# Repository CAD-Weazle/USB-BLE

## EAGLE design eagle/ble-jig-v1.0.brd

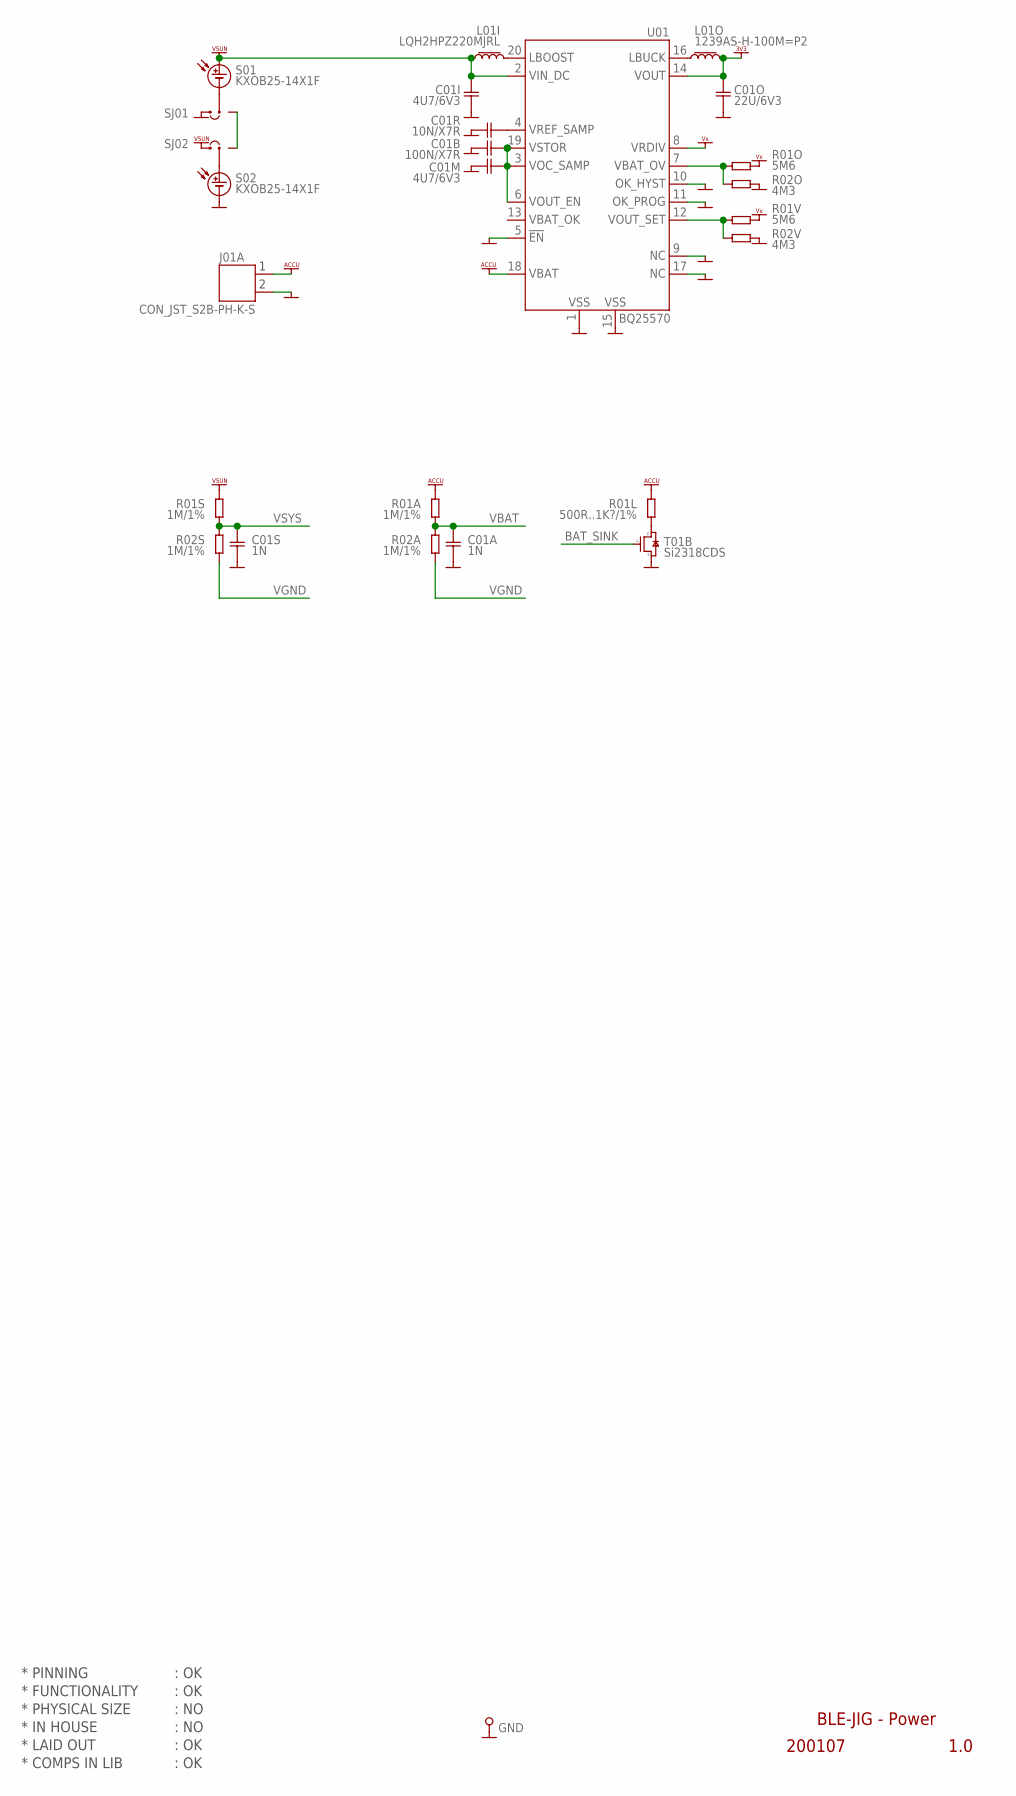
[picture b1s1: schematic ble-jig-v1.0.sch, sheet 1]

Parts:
C01A, C01S: 1N; CAP0402
C01B: 100N/X7R; CAP0402
C01I, C01M: 4U7/6V3; CAP0402
C01O: 22U/6V3; CAP0402
C01R: 10N/X7R; CAP0402
GND: PIN_TEST; HOLE_PTH_0.8MM
J01A: CON_JST_S2B-PH-K-S
L01I: LQH2HPZ220MJRL; L_1008
L01O: 1239AS-H-100M=P2; L_1008
R01A, R01S, R02A, R02S: 1M/1%; RES0402
R01L: 500R..1K?/1%; RES0603
R01O, R01V: 5M6; RES0402
R02O, R02V: 4M3; RES0402
S01, S02: KXOB25-14X1F
SJ01, SJ02: SJ3SJ3-S; SJ3-S
T01B: Si2318CDS; NFET_SOT23
U01: BQ25570; VQFN20

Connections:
ACCU: J01A.1, R01A.2, R01L.2, U01.18 (18.VBAT)
BAT_SINK: T01B.1 (G1); also elsewhere on the board
GND: C01A.2, C01B.2, C01I.2, C01M.2, C01O.2, C01R.2, C01S.2, GND.1, J01A.2, R02O.2, R02V.2, S02.2, SJ01.1, T01B.2 (S2), U01.1 (1.VSS), U01.5 (5.!EN), U01.9 (9.NC), U01.10 (10.OK_HYST), U01.11 (11.OK_PROG), U01.15 (15.VSS), U01.17 (17.NC), U01.TP (15.VSS), U01.V1 (15.VSS), U01.V2 (15.VSS), U01.V3 (15.VSS), U01.V4 (15.VSS); also elsewhere on the board
unnamed: S01.2, SJ01.2
unnamed: S02.1, SJ02.2
unnamed: SJ01.3, SJ02.3
unnamed: R01L.1, T01B.3 (D3)
unnamed: C01R.1, U01.4 (4.VREF_SAMP)
unnamed: L01I.2, U01.20 (20.LBOOST)
unnamed: L01O.1, U01.16 (16.LBUCK)
VBAT: C01A.1, R01A.1, R02A.2; also elsewhere on the board
VBAT_OV: R01O.2, R02O.1, U01.7 (7.VBAT_OV)
VDD_3V3: C01O.1, L01O.2, U01.14 (14.VOUT); also elsewhere on the board
VGND: R02A.1, R02S.1; also elsewhere on the board
VOUT_SET: R01V.2, R02V.1, U01.12 (12.VOUT_SET)
VSTOR: C01B.1, C01M.1, U01.3 (3.VOC_SAMP), U01.6 (6.VOUT_EN), U01.19 (19.VSTOR)
VSUN: C01I.1, L01I.1, R01S.2, S01.1, SJ02.1, U01.2 (2.VIN_DC)
VSYS: C01S.1, R01S.1, R02S.2; also elsewhere on the board
VX: R01O.1, R01V.1, U01.8 (8.VRDIV)

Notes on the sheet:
* PINNING
* FUNCTIONALITY
* PHYSICAL SIZE
* LAID OUT
* COMPS IN LIB
* IN HOUSE
BLE-JIG - Power
200107
1.0
: OK
: NO

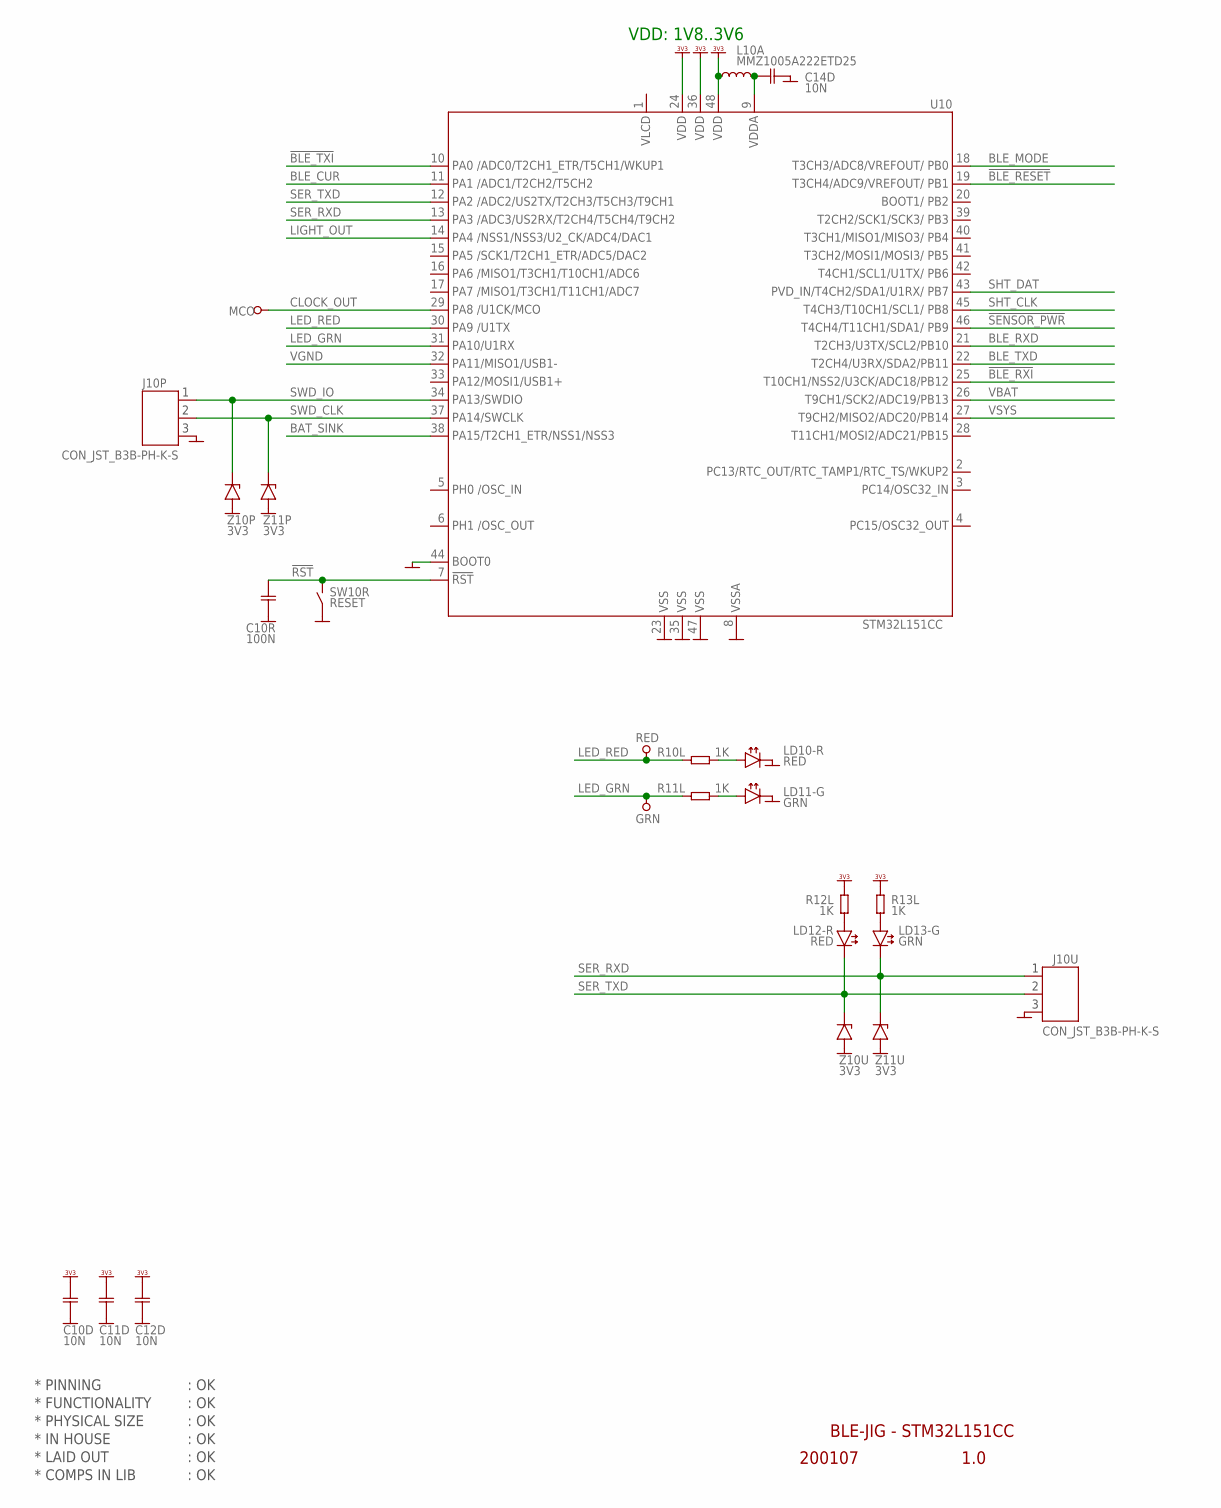
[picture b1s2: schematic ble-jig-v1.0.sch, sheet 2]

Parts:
C10D, C11D, C12D, C14D: 10N; CAP0402
C10R: 100N; CAP0402
GRN: PIN_TEST_0.6MM; HOLE_PTH_0.6MM
J10P, J10U: CON_JST_B3B-PH-K-S
L10A: MMZ1005A222ETD25; L_0402
LD10-R, LD12-R: RED; LED_SMD_0603
LD11-G, LD13-G: GRN; LED_SMD_0603
MCO: PIN_TEST; HOLE_PTH_0.8MM
R10L, R11L, R12L, R13L: 1K; RES0402
RED: PIN_TEST_0.6MM; HOLE_PTH_0.6MM
SW10R: RESET; SWITCH_PUSHBUTTON_EVP-AVAA1A
U10: STM32L151CC; LQFP48
Z10P, Z10U, Z11P, Z11U: 3V3; ZENER_SOD80

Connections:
!BLE_RESET: U10.19 (19.PB1); also elsewhere on the board
!BLE_RXI: U10.25 (25.PB12); also elsewhere on the board
!BLE_TXI: U10.10 (10.PA0); also elsewhere on the board
!RST: C10R.1, SW10R.1 (1-2), U10.7 (7.!RST)
!SENSOR_PWR: U10.46 (46.PB9); also elsewhere on the board
BAT_SINK: U10.38 (38.PA15); also elsewhere on the board
BLE_CUR: U10.11 (11.PA1); also elsewhere on the board
BLE_MODE: U10.18 (18.PB0); also elsewhere on the board
BLE_RXD: U10.21 (21.PB10); also elsewhere on the board
BLE_TXD: U10.22 (22.PB11); also elsewhere on the board
CLOCK_OUT: MCO.1, U10.29 (29.PA8)
GND: C10D.2, C10R.2, C11D.2, C12D.2, C14D.2, J10P.3, J10U.3, LD10-R.C, LD11-G.C, SW10R.2 (3-4), U10.8 (8.GND), U10.23 (23.GND), U10.35 (35.GND), U10.44 (44.BOOT0), U10.47 (47.GND), Z10P.1 (+), Z10U.1 (+), Z11P.1 (+), Z11U.1 (+); also elsewhere on the board
LED_GRN: GRN.1, R11L.1, U10.31 (31.PA10)
LED_RED: R10L.1, RED.1, U10.30 (30.PA9)
LIGHT_OUT: U10.14 (14.PA4); also elsewhere on the board
unnamed: LD13-G.A, R13L.2
unnamed: LD12-R.A, R12L.2
unnamed: LD11-G.A, R11L.2
unnamed: LD10-R.A, R10L.2
SER_RXD: J10U.1, LD13-G.C, U10.13 (13.PA3), Z11U.2 (-)
SER_TXD: J10U.2, LD12-R.C, U10.12 (12.PA2), Z10U.2 (-)
SHT_CLK: U10.45 (45.PB8); also elsewhere on the board
SHT_DAT: U10.43 (43.PB7); also elsewhere on the board
SWD_CLK: J10P.2, U10.37 (37.PA14), Z11P.2 (-)
SWD_IO: J10P.1, U10.34 (34.PA13), Z10P.2 (-)
VBAT: U10.26 (26.PB13); also elsewhere on the board
VDDA: C14D.1, L10A.2, U10.9 (9.VDD)
VDD_3V3: C10D.1, C11D.1, C12D.1, L10A.1, R12L.1, R13L.1, U10.24 (24.VDD), U10.36 (36.VDD), U10.48 (48.VDD); also elsewhere on the board
VGND: U10.32 (32.PA11); also elsewhere on the board
VSYS: U10.27 (27.PB14); also elsewhere on the board

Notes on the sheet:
* PINNING
* FUNCTIONALITY
* PHYSICAL SIZE
* LAID OUT
* COMPS IN LIB
* IN HOUSE
: OK
BLE-JIG - STM32L151CC
200107
1.0
VDD: 1V8..3V6

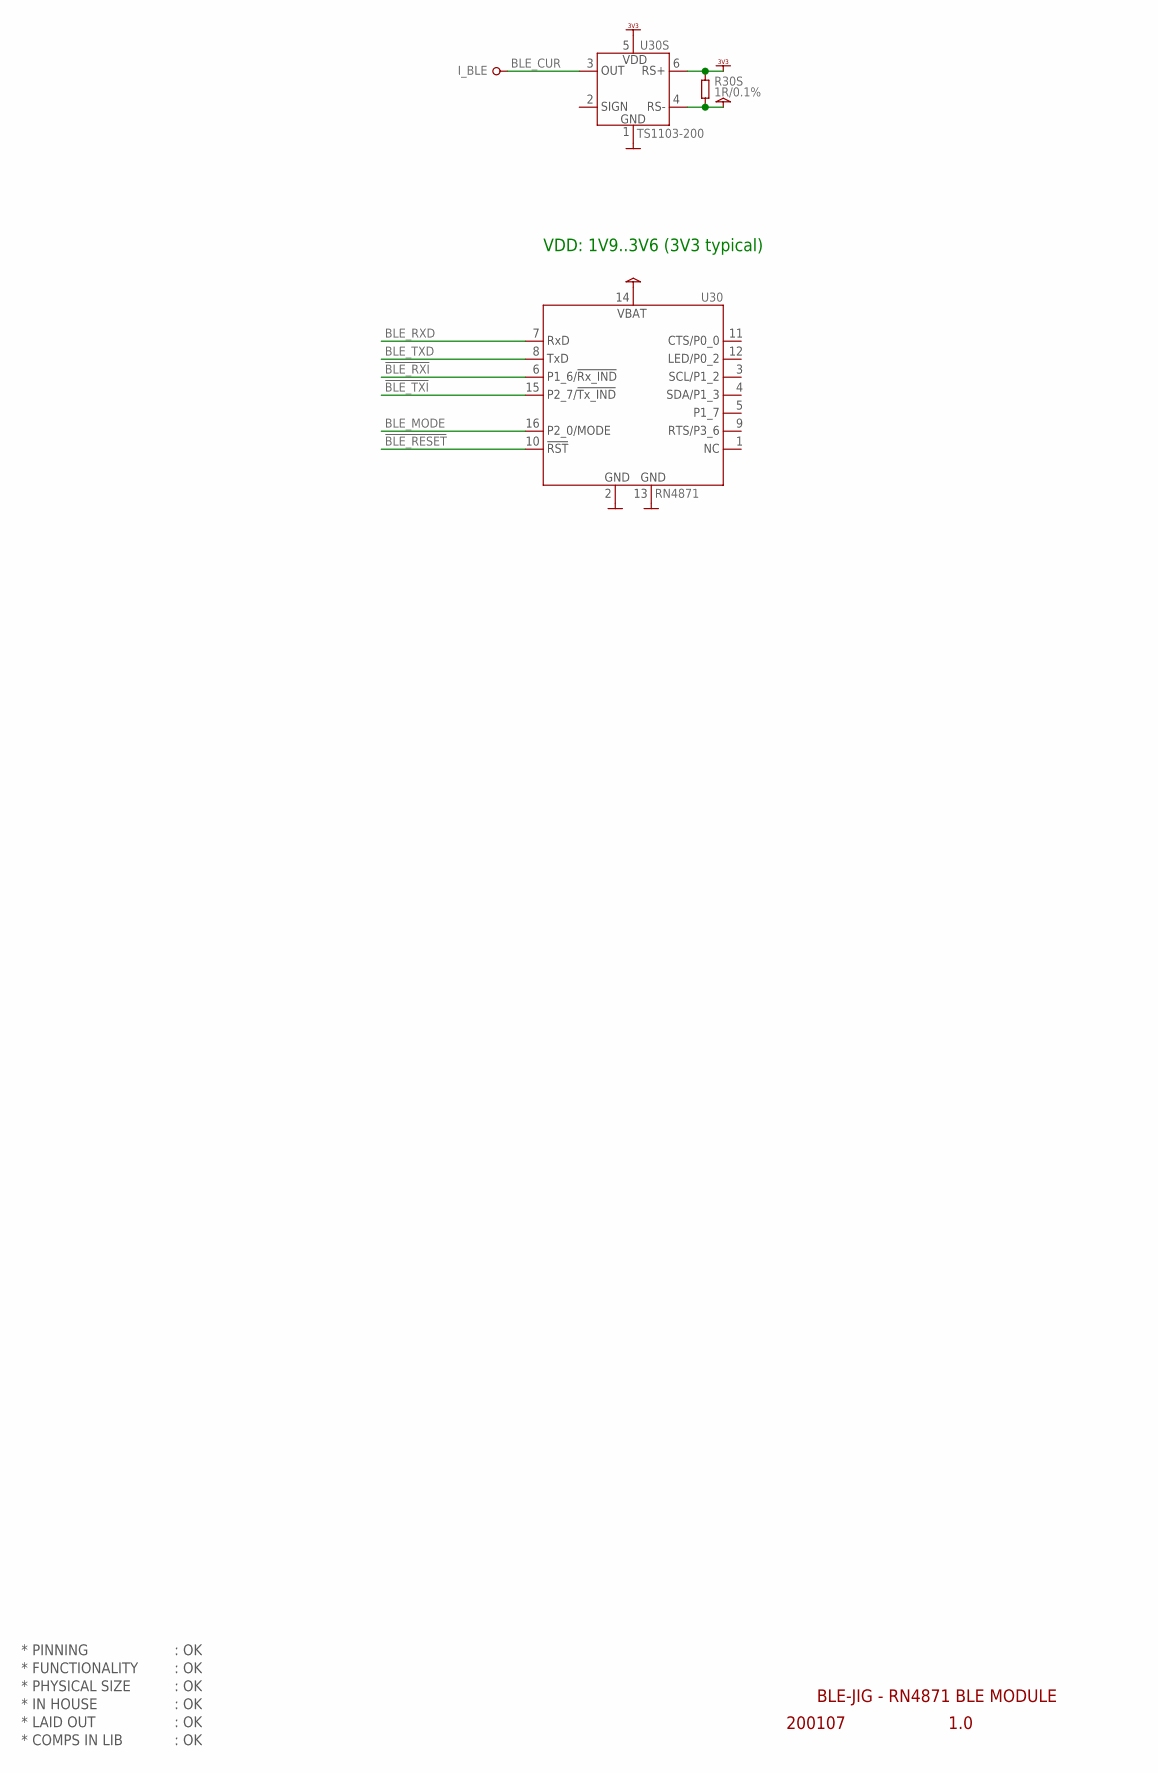
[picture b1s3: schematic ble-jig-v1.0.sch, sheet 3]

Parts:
I_BLE: PIN_TEST; HOLE_PTH_0.8MM
R30S: 1R/0.1%; RES0603
U30: RN4871
U30S: TS1103-200; SOT23-6

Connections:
!BLE_RESET: U30.10 (10.!RST); also elsewhere on the board
!BLE_RXI: U30.6 (6.P1_6); also elsewhere on the board
!BLE_TXI: U30.15 (15.P2_7); also elsewhere on the board
BLE_CUR: I_BLE.1, U30S.3 (3.OUT); also elsewhere on the board
BLE_MODE: U30.16 (16.P2_0); also elsewhere on the board
BLE_RXD: U30.7 (7.RXD); also elsewhere on the board
BLE_TXD: U30.8 (8.TXD); also elsewhere on the board
GND: U30.2 (2.GND), U30.13 (13.GND), U30S.1 (1.GND); also elsewhere on the board
VCC: R30S.2, U30.14 (14.VBAT), U30S.4 (4.RS-)
VDD_3V3: R30S.1, U30S.5 (5.VDD), U30S.6 (6.RS+); also elsewhere on the board

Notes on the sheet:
* PINNING
* FUNCTIONALITY
* PHYSICAL SIZE
* LAID OUT
* COMPS IN LIB
* IN HOUSE
1.0
BLE-JIG - RN4871 BLE MODULE
200107
: OK
VDD: 1V9..3V6 (3V3 typical)

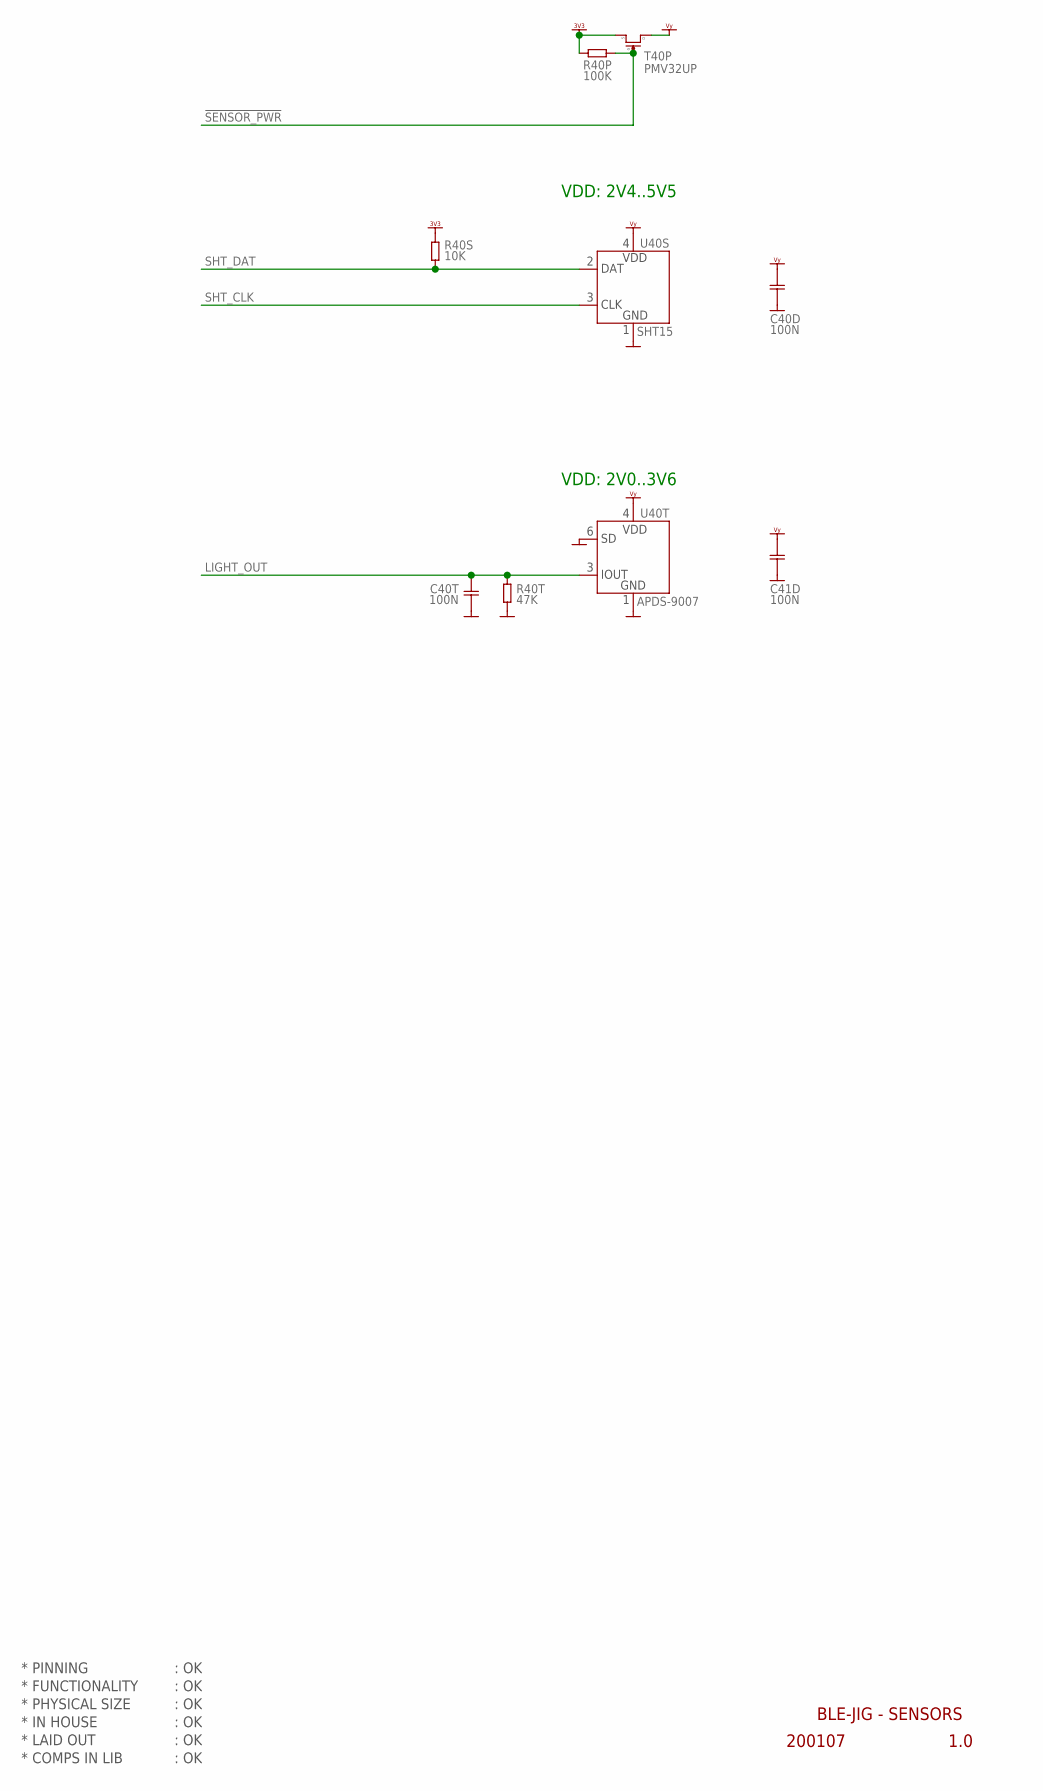
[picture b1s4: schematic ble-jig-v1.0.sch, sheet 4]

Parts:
C40D, C40T, C41D: 100N; CAP0402
R40P: 100K; RES0402
R40S: 10K; RES0402
R40T: 47K; RES0402
T40P: PMV32UP; PFET_SOT23
U40S: SHT15
U40T: APDS-9007

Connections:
!SENSOR_PWR: R40P.2, T40P.1 (G); also elsewhere on the board
GND: C40D.2, C40T.2, C41D.2, R40T.2, U40S.1 (1.GND), U40T.1 (1.GND), U40T.6 (6.SD); also elsewhere on the board
LIGHT_OUT: C40T.1, R40T.1, U40T.3 (3.IOUT); also elsewhere on the board
SHT_CLK: U40S.3 (3.CLK); also elsewhere on the board
SHT_DAT: R40S.2, U40S.2 (2.DAT); also elsewhere on the board
VDD_3V3: R40P.1, R40S.1, T40P.2 (S); also elsewhere on the board
VY: C40D.1, C41D.1, T40P.3 (D), U40S.4 (4.VDD), U40T.4 (4.VDD)

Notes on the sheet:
* PINNING
* FUNCTIONALITY
* PHYSICAL SIZE
* LAID OUT
* COMPS IN LIB
* IN HOUSE
1.0
BLE-JIG - SENSORS
200107
: OK
VDD: 2V0..3V6
VDD: 2V4..5V5

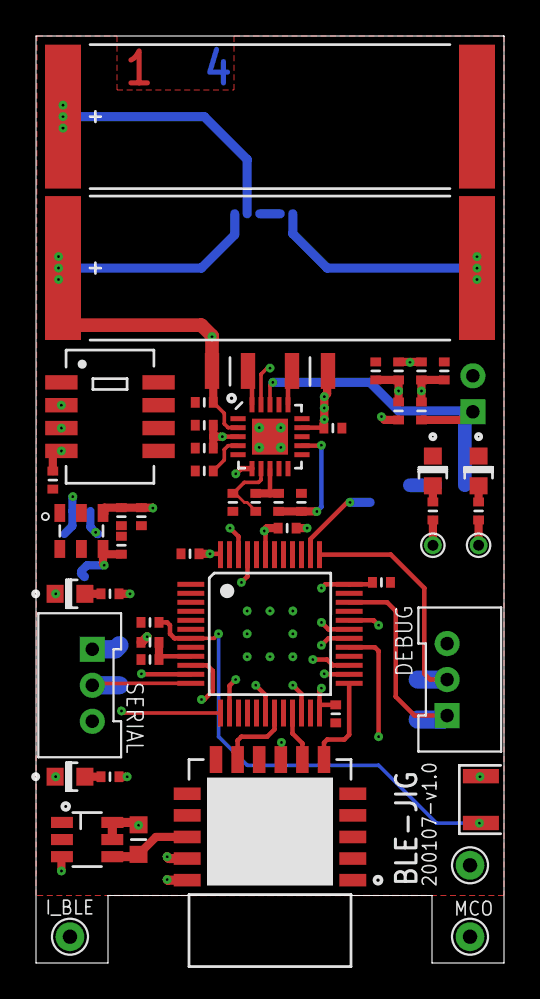
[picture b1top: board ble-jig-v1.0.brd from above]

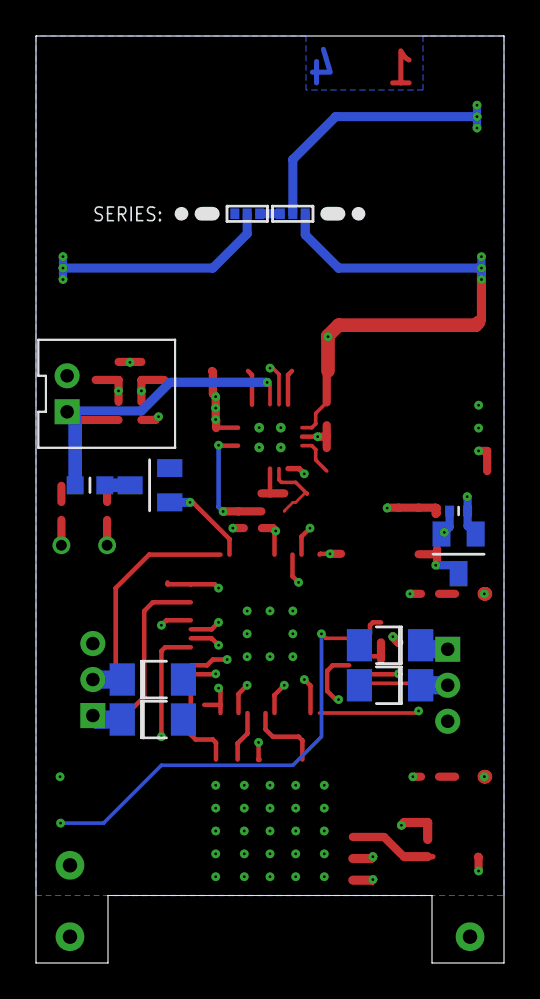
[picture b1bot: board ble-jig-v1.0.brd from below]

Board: 4 copper layers, 26.0 x 51.5 mm, 64 parts (11 on the bottom side), 45 nets.

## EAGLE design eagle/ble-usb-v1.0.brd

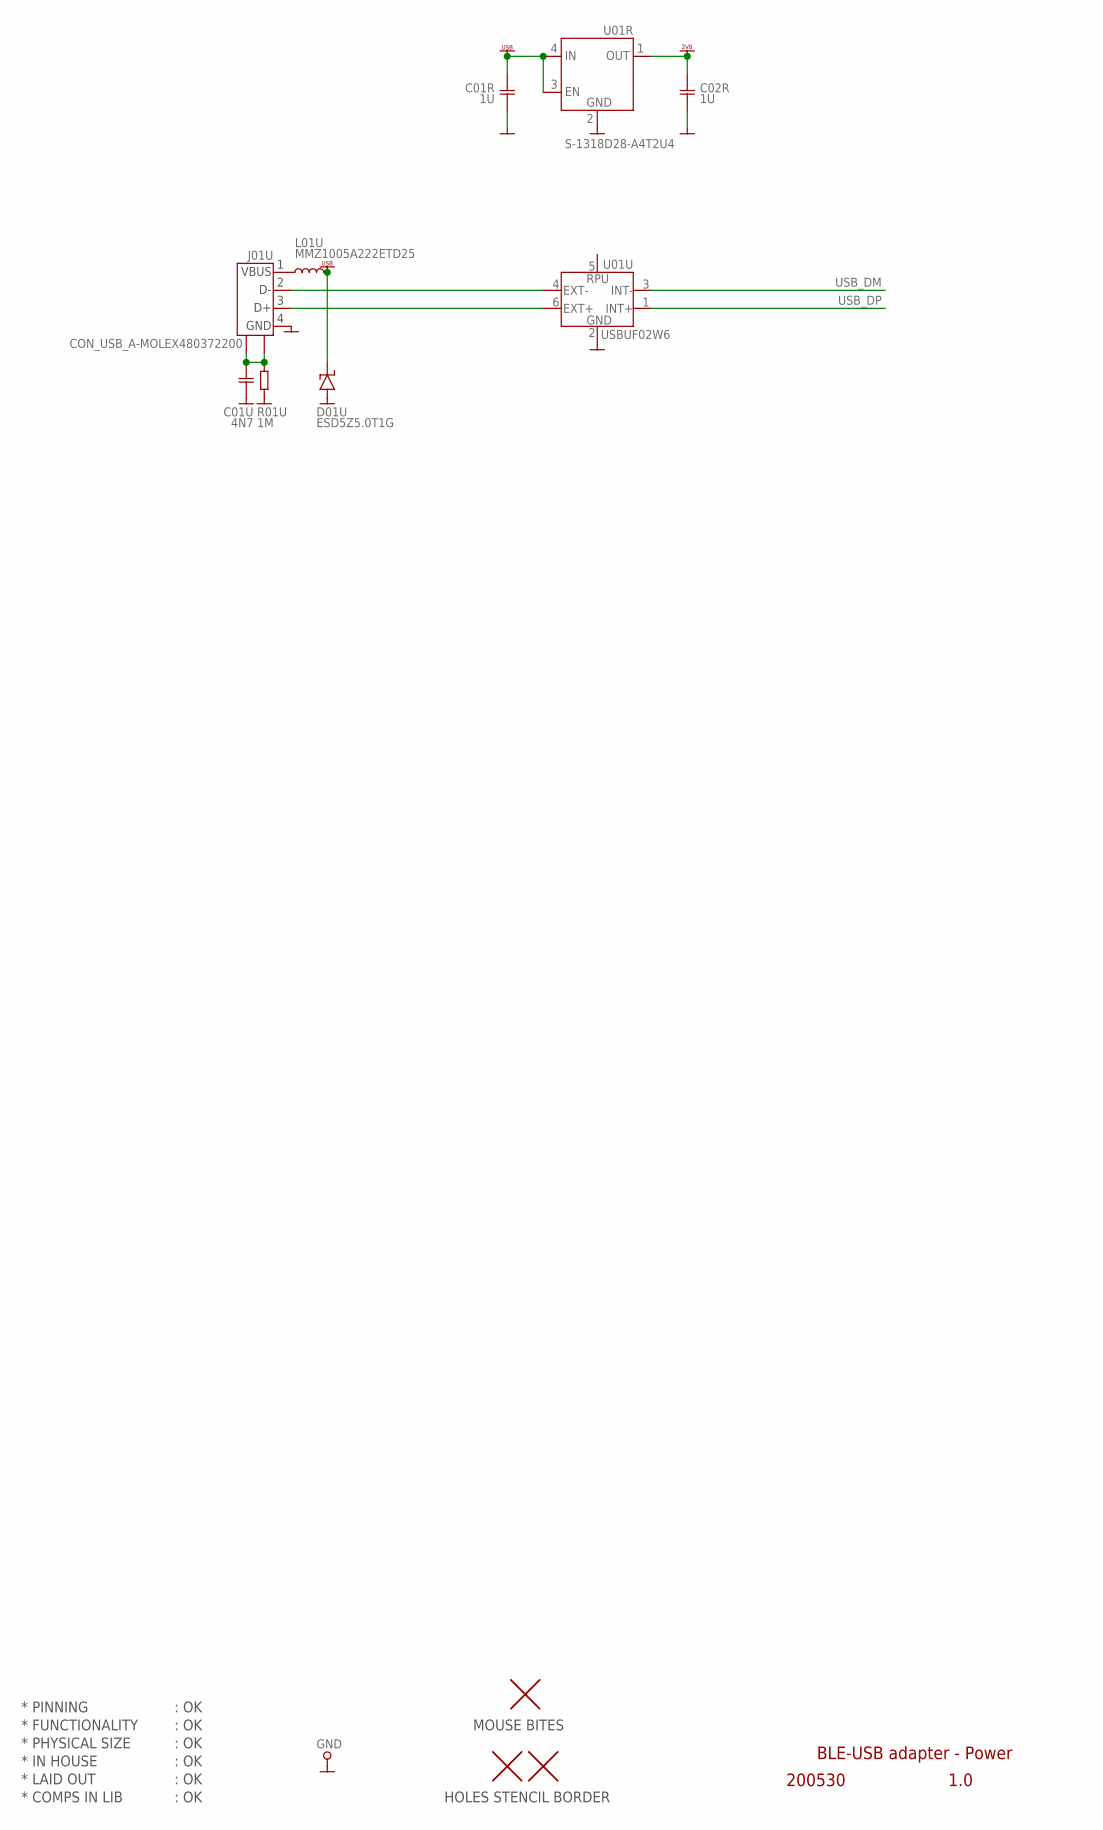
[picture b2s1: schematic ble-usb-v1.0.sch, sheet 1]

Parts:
C01R, C02R: 1U; CAP0402
C01U: 4N7; CAP0402
D01U: ESD5Z5.0T1G; DIODE_SOD523
GND: PIN_TEST_0.6MM; HOLE_PTH_0.6MM
H1, H2: HOLE_NPTH_3.0MM-STENCILBORDER; HOLE_NPTH_3,0MM-STECILBORDER
H10: HOLE_MOUSEBITES; HOLE_NPTH_0.5MM
J01U: CON_USB_A-MOLEX480372200
L01U: MMZ1005A222ETD25; L_0402
R01U: 1M; RES0402
U01R: S-1318D28-A4T2U4; HSNT-4-B
U01U: USBUF02W6; SOT323-6L

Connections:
GND: C01R.2, C01U.2, C02R.2, D01U.A, GND.1, J01U.4 (4.GND), R01U.2, U01R.2 (2.GND), U01R.5 (2.GND), U01U.2 (2.GND); also elsewhere on the board
unnamed: J01U.1 (1.VBUS), L01U.1
unnamed: J01U.2 (2.D-), U01U.4 (4.EXT-)
unnamed: J01U.3 (3.D+), U01U.6 (6.EXT+)
USB_CHASSIS: C01U.1, J01U.CASE1 (5.CASE), J01U.CASE2 (6.CASE), R01U.1
USB_DM: U01U.3 (3.INT-); also elsewhere on the board
USB_DP: U01U.1 (1.INT+); also elsewhere on the board
VDD_2V8: C02R.1, U01R.1 (1.OUT); also elsewhere on the board
VDD_USB: C01R.1, D01U.C, L01U.2, U01R.3 (3.EN), U01R.4 (4.IN)

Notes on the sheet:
* PINNING
* FUNCTIONALITY
* PHYSICAL SIZE
* LAID OUT
* COMPS IN LIB
* IN HOUSE
BLE-USB adapter - Power
200530
1.0
: OK
HOLES STENCIL BORDER
MOUSE BITES

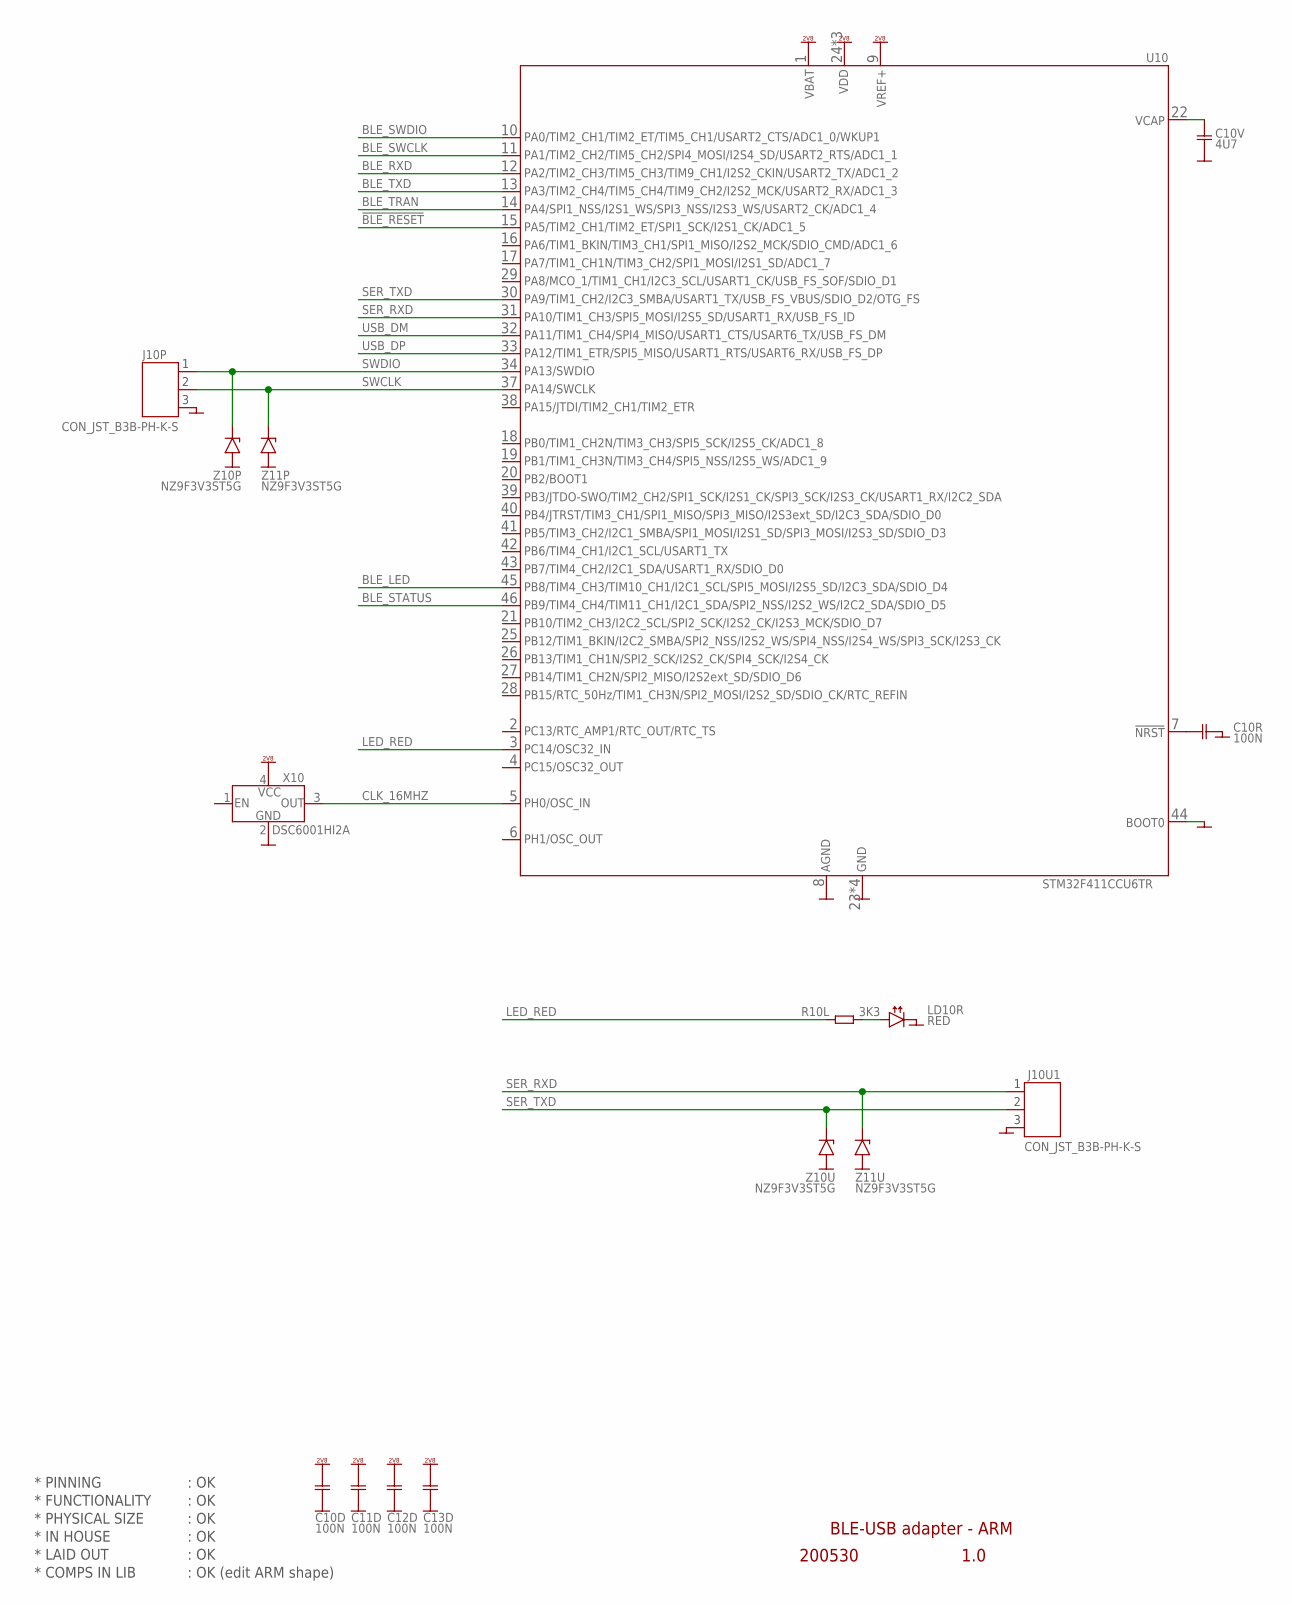
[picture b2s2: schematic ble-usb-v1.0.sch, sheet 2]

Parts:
C10D, C10R, C11D, C12D, C13D: 100N; CAP0402
C10V: 4U7; CAP0402
J10P, J10U1: CON_JST_B3B-PH-K-S
LD10R: RED; LED_SMD_0402
R10L: 3K3; RES0402
U10: STM32F411CCU6TR; VQFN48
X10: DSC6001HI2A; VFLGA4_1.6X1.2MM
Z10P, Z10U, Z11P, Z11U: NZ9F3V3ST5G; ZENER_SOD923

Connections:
!BLE_RESET: U10.15 (PA5); also elsewhere on the board
BLE_LED: U10.45 (PB8); also elsewhere on the board
BLE_RXD: U10.12 (PA2); also elsewhere on the board
BLE_STATUS: U10.46 (PB9); also elsewhere on the board
BLE_SWCLK: U10.11 (PA1); also elsewhere on the board
BLE_SWDIO: U10.10 (PA0); also elsewhere on the board
BLE_TRAN: U10.14 (PA4); also elsewhere on the board
BLE_TXD: U10.13 (PA3); also elsewhere on the board
CLK_16MHZ: U10.5 (PH0), X10.3 (3.OUT)
GND: C10D.1, C10R.2, C10V.2, C11D.2, C12D.2, C13D.2, J10P.3, J10U1.3, LD10R.C, U10.8 (VSSA), U10.23 (VSS), U10.35 (VSS), U10.44 (BOOT0), U10.47 (VSS), U10.TP (VSS), X10.2 (2.GND), Z10P.2 (A), Z10U.2 (A), Z11P.2 (A), Z11U.2 (A); also elsewhere on the board
LED_RED: R10L.1, U10.3 (PC14)
unnamed: C10R.1, U10.7 (NRST)
unnamed: LD10R.A, R10L.2
unnamed: C10V.1, U10.22 (VCAP)
SER_RXD: J10U1.1, U10.31 (PA10), Z11U.1 (C)
SER_TXD: J10U1.2, U10.30 (PA9), Z10U.1 (C)
SWCLK: J10P.2, U10.37 (PA14), Z11P.1 (C)
SWDIO: J10P.1, U10.34 (PA13), Z10P.1 (C)
USB_DM: U10.32 (PA11); also elsewhere on the board
USB_DP: U10.33 (PA12); also elsewhere on the board
VDD_2V8: C10D.2, C11D.1, C12D.1, C13D.1, U10.1 (VBAT), U10.9 (VREF+), U10.24 (VDD), U10.36 (VDD), U10.48 (VDD), X10.4 (4.VCC); also elsewhere on the board

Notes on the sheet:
BLE-USB adapter - ARM
200530
1.0
* PINNING
* FUNCTIONALITY
* PHYSICAL SIZE
* LAID OUT
* COMPS IN LIB
* IN HOUSE
: OK
: OK (edit ARM shape)

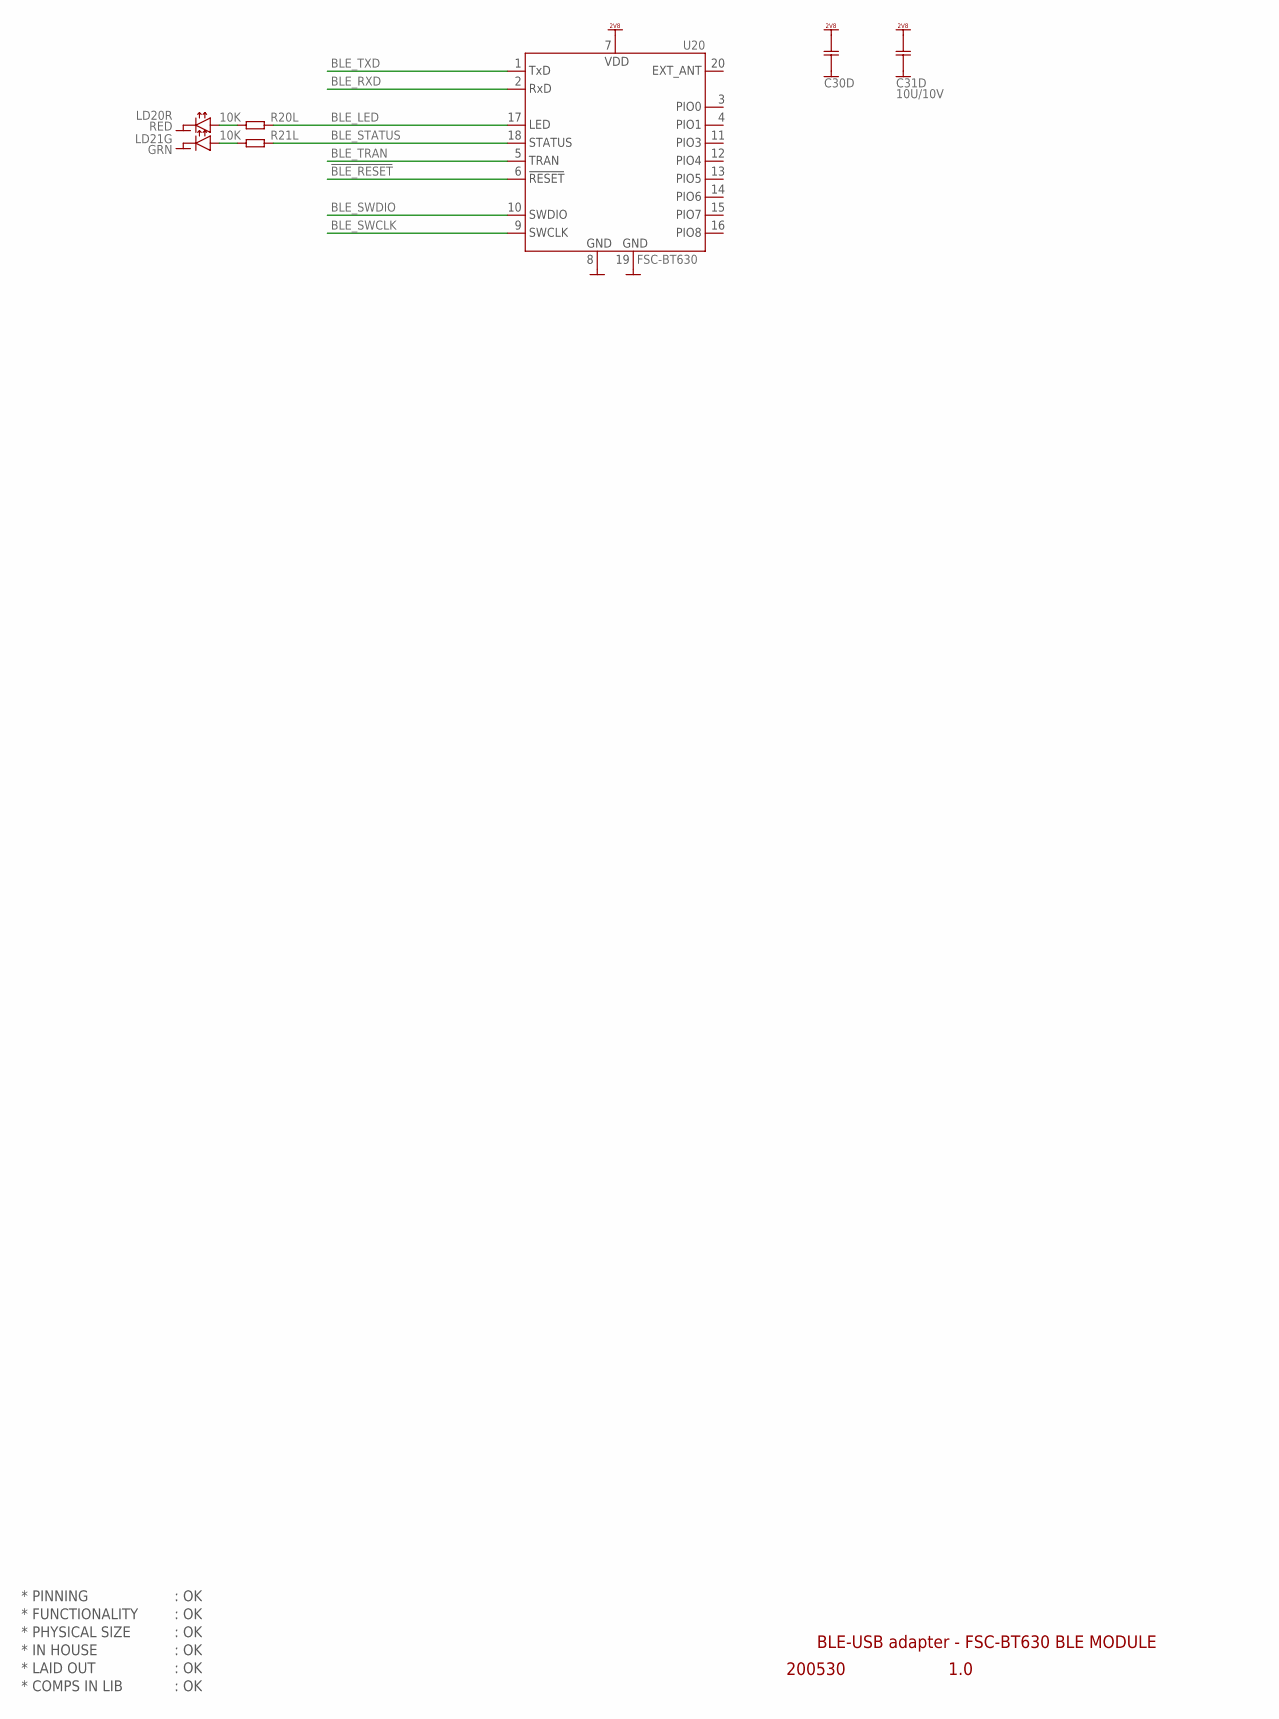
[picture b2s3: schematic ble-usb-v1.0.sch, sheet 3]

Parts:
C30D: 100N; CAP0402
C31D: 10U/10V; CAP0402
LD20R: RED; LED_SMD_0402
LD21G: GRN; LED_SMD_0402
R20L, R21L: 10K; RES0402
U20: FSC-BT630

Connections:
!BLE_RESET: U20.6 (6.!RESET); also elsewhere on the board
BLE_LED: R20L.1, U20.17 (17.LED); also elsewhere on the board
BLE_RXD: U20.2 (2.RXD); also elsewhere on the board
BLE_STATUS: R21L.1, U20.18 (18.STATUS); also elsewhere on the board
BLE_SWCLK: U20.9 (9.SWCLK); also elsewhere on the board
BLE_SWDIO: U20.10 (10.SWDIO); also elsewhere on the board
BLE_TRAN: U20.5 (5.TRAN); also elsewhere on the board
BLE_TXD: U20.1 (1.TXD); also elsewhere on the board
GND: C30D.2, C31D.2, LD20R.C, LD21G.C, U20.8 (8.GND), U20.19 (19.GND); also elsewhere on the board
unnamed: LD21G.A, R21L.2
unnamed: LD20R.A, R20L.2
VDD_2V8: C30D.1, C31D.1, U20.7 (7.VDD); also elsewhere on the board

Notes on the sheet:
* PINNING
* FUNCTIONALITY
* PHYSICAL SIZE
* LAID OUT
* COMPS IN LIB
* IN HOUSE
1.0
BLE-USB adapter - FSC-BT630 BLE MODULE
200530
: OK

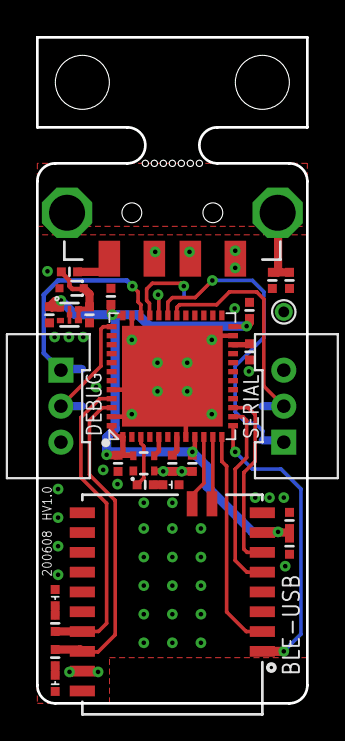
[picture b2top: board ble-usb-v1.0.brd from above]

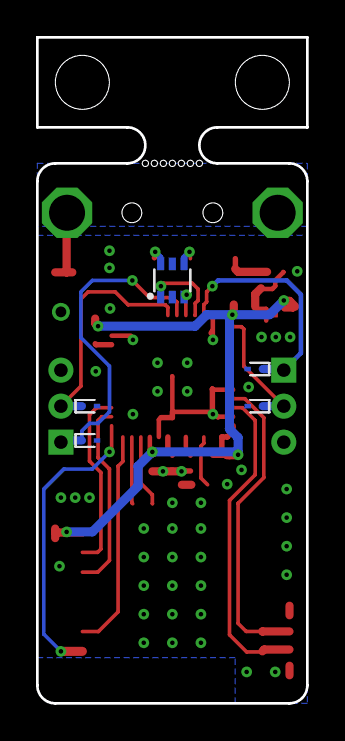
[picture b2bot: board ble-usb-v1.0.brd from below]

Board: 4 copper layers, 15.0 x 37.0 mm, 36 parts (5 on the bottom side), 28 nets.
